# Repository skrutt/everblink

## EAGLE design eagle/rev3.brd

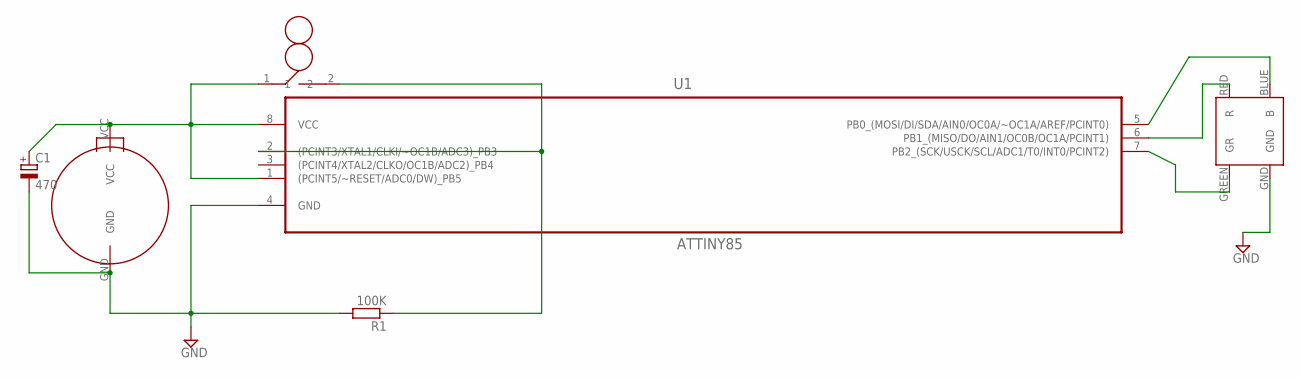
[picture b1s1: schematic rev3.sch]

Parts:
C1: 470; E2,5-6
R1: 100K; 0207/10
U1: ATTINY85; DIP254P762X533-8; MPN ATTINY85
U$1: CR2032_2PIN
U$2: RGB_4PIN; 5MM_RGB
U$3: BALL_SWITCH; BALL_SW

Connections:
BLUE: U1.7 (PB2_(SCK/USCK/SCL/ADC1/T0/INT0/PCINT2)), U$2.GREEN (GR)
GND: C1.-, R1.2, U1.4 (GND), U$1.GND, U$2.GND
GREEN: U1.6 (PB1_(MISO/DO/AIN1/OC0B/OC1A/PCINT1)), U$2.RED (R)
PB3: R1.1, U1.2 ((PCINT3/XTAL1/CLKI/~OC1B/ADC3)_PB3), U$3.2
RED: U1.5 (PB0_(MOSI/DI/SDA/AIN0/OC0A/~OC1A/AREF/P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), U$2.BLUE (B)
VCC: C1.+, U1.1 ((PCINT5/~RESET/ADC0/DW)_PB5), U1.8 (VCC), U$1.VCC, U$3.1

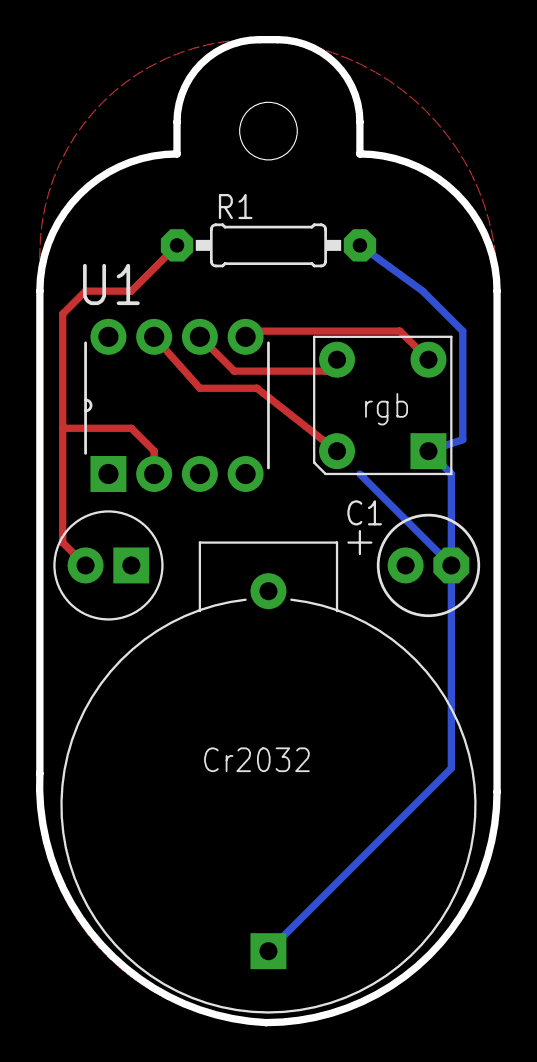
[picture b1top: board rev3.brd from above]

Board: 2 copper layers, 25.4 x 54.6 mm, 6 parts (0 on the bottom side), 6 nets.

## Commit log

2015-10-03 :octocat: Added .gitattributes & .gitignore files
2015-10-03 add design files
    first commit
2015-10-04 first try at enclosure
2015-10-28 energy analysis
2015-10-28 Revert "energy analysis"
    This reverts commit ab7d954a83c0ef110041ad027e820ef9c1ff2a74.
2015-10-28 Revert "Revert "energy analysis""
    This reverts commit 08b77816748d06c361087d8c7a843ec42290c0a4.
2015-10-28 energy analsis
    unit upside down, ie no pullup current
